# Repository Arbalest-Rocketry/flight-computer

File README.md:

# The Arbalest Goose 4 Avionics Systems & Flight Computer Software by `Leroy Musa`

This repository contains the code and documentation for the flight computer used for our 2 Stage High Power Rocket set to launch at Launch Canada 2024 

## Flight Computer
Our flight computer setup includes two unique PCBs for different rocket stages.

Stage 1 ("BLOB"): This PCB handles all operations for the first stage of the flight, ensuring smooth launch and initial ascent.

Stage 2 (Prototyping Board): This board not only manages the second stage but also controls RunCam devices for onboard video recording. Despite its prototyping nature, it functions just as effectively as the Stage 1 computer.

This dual-PCB setup ensures specialized and reliable performance throughout the entire flight.
<div style="text-align: center;">

</div>

## Components
- Microcontroller: [Teensy 4.1](https://www.pjrc.com/store/teensy41.html)
- Sensors:
  - Altimeter: [Adafruit BMP280](https://www.adafruit.com/product/2651)
  - IMU (Inertial Measurement Unit): [Adafruit BNO055](https://www.adafruit.com/product/4646)
  - GPS Module: [SparkFun GNSS Receiver Breakout - MAX-M10S (Qwiic)](https://www.sparkfun.com/products/18037)
  - SD Breakout: [Adafruit SPI Flash SD Card - XTSD 512 MB](https://www.adafruit.com/product/4899)
- Communication: [Adafruit LoRa RFM9X](https://www.adafruit.com/product/3072)
- Our COTS (Commercial Off-The-Shelf) Flight Computer: [Featherweight Blue Raven](https://www.featherweightaltimeters.com/blue-raven-altimeter.html)
(left)
- Our COTS GPS: [Featherweight GPS Tracker](https://www.featherweightaltimeters.com/featherweight-gps-tracker.html) (right)
<div style="text-align: center;">

</div>

## Avionics Bay Design by `Jordan Birley` and `Caelan Babenko`
The electronics mount CAD design showcases the placement of PCBs within the rocket's fuselage. This design ensures the flight computer's and associated components' proper integration and protection.

<div style="text-align: center;">

</div>

## Testing Setup
Here's an image showing my testing setup for the flight computer(left) and ground station(right):

<div style="text-align: center;">

</div>

## PCBv2.0 Schematics by `Baseer Yousufzai`
Pictures showing our current **Arbalest Flight Computer** schematics layout
<div style="text-align: center;">
  
</div>
<div style="text-align: center;">

</div>

## IRLv2.0
<div style="text-align: center;">

</div>

## PCBv1.0 Schematics by `Baseer Yousufzai`
Pictures showing v1.0 of our **Arbalest Flight Computer** schematics layout
<div style="text-align: center;">
  
</div>
<div style="text-align: center;">

</div>

## IRLv1.0
<div style="text-align: center;">

</div>

## PCB Improvements

This table outlines the major improvements made from PCB v1.0 to PCB v2.0.

| feature                      | pcb v1.0                                  | pcb v2.0                                        | improvement description                                    |
|------------------------------|-------------------------------------------|-------------------------------------------------|------------------------------------------------------------|
| layering                     | single-layer design                       | multi-layer design                              | enhanced routing and reduced interference                  |
| power supply management      | basic power supply connections            | advanced power routing                          | improved power stability and distribution                  |
| lora module         | back right                             | front top right corner                                | better isolation from other components for improved signal quality & better placement for electronics mount                   |

## How it works 
Simple Illustration 
<div style="text-align: center;">
  
</div>

## Arbalest Flight Computer Integration Guide

### Overview

This document provides a detailed description of the Arbalest Flight Computer setup as depicted in the schematic. The system integrates four 3.7V 650mAh LiPo batteries, a screw switch, and three Runcam Split 4 cameras connected to the Arbalest Flight Computer. The flight computer controls four pyro channels specifically designed for parachute deployment.

### Components

1. **Arbalest Flight Computer**
2. **3.7V 650mAh LiPo Batteries (4x)**
3. **Screw Switch**
4. **Runcam Split 4 Cameras (3x)**
5. **Pyro Channels (4x) for Parachute Deployment**

### Wiring Diagram

The wiring diagram consists of the following connections:
- Power supply wiring from the batteries
- Activation of switch wiring
- Camera connections
- Pyro channel connections for parachute deployment

### Power Supply

The power supply section is crucial for powering the flight computer and the connected components.

1. **LiPo Batteries:**
   - Four 3.7V 650mAh LiPo batteries are wired in series parallel to form a 7.4V 1950mAh power pack.
   - **Series Connection:** Two pairs of two batteries connected in series, resulting in two 7.4V packs.
   - **Parallel Connection:** These two 7.4V packs are connected in parallel to increase the capacity to 1950mAh.

2. **Wiring:**
   - The positive terminal of the first battery is connected to the positive terminal of the second battery.
   - The negative terminal of the second battery is connected to the positive terminal of the third battery.
   - The negative terminal of the third battery is connected to the positive terminal of the fourth battery.
   - The negative terminal of the fourth battery is connected back to the system ground.

3. **Screw Switch:**
   - The main power from the batteries is routed through a screw switch to control the power supply to the entire system.
   - The positive wire from the battery pack connects to one terminal of the screw switch.
   - The other terminal of the screw switch connects to the power input of the Arbalest Flight Computer.

### Pyro Channels for Parachute Deployment

The flight computer controls four pyro channels for parachute deployment.

1. **Connections:**
   - Each pyro channel (1 to 4) has two wires: one connected to the flight computer and the other to the pyro device.
   - The flight computer sends a signal to activate the pyrotechnic devices through these wires.

## Conclusion

The integration of the Arbalest Flight Computer with the LiPo batteries, screw switch, Runcam Split 4 cameras, and pyro channels provides a robust system for managing various flight operations, including parachute deployment. 

# Transceiver Test w/ RC plane
<div style="text-align: center;">

</div>

## Low Noise Amplifiers

The low noise amplifiers (LNAs) are crucial components in the Arbalest flight computer's communication system. They are used to amplify weak signals received from the rocket, ensuring they are strong enough to be processed and analyzed. The following images show the setup of the LNAs connected to the Teensy 4.1 microcontroller board:

<div style="text-align: center;">

</div>

### Function of the Low Noise Amplifiers

Low noise amplifiers are designed to amplify weak signals received by the antenna with minimal addition of noise. This is essential in communication systems where signal strength can be significantly reduced due to distance, atmospheric conditions, and other interference factors.

### How the Amplifier and Filter Work

The LNA circuit shown in the images is connected to the LoRa (Long Range) communication module to improve the signal-to-noise ratio. Here’s a detailed explanation of the process:

1. **Signal Reception:**
   - The weak signal received by the antenna is fed into the LNA. This signal is typically very weak and can be easily lost in the noise.

2. **Amplification:**
   - The LNA amplifies the weak signal. The primary goal is to increase the signal strength without adding significant noise. This is achieved through the careful design of the amplifier circuit, using high-quality components that contribute minimal noise.

3. **Filtering:**
   - After amplification, the signal may pass through a filter to remove unwanted frequencies or noise that might have been introduced during amplification. This ensures that only the desired signal is sent to the next stage of the communication system.

4. **Enhanced Signal:**
   - The enhanced signal, now much stronger and clearer, is fed into the LoRa module. The LoRa module can now process this signal more effectively, providing reliable communication over long distances.

### Connecting to LoRa for Increased Gain

The LoRa communication module is known for its ability to transmit data over long distances with low power consumption. By connecting the output of the LNA to the LoRa module, we achieve the following benefits:

- **Increased Range:**
  - The amplified signal can travel greater distances without degradation, improving the overall range of the communication system.

- **Improved Signal Quality:**
  - The higher signal-to-noise ratio achieved through amplification and filtering results in better signal quality, reducing the likelihood of errors in data transmission.

- **Enhanced Reliability:**
  - With stronger and clearer signals, the communication link becomes more reliable, which is critical for mission success in rocketry.

---
# To Infinity and Beyond

---
# Authors
- [Leroy Musa](mailto:musaleroyohio@gmail.com) - Author & Maintainer

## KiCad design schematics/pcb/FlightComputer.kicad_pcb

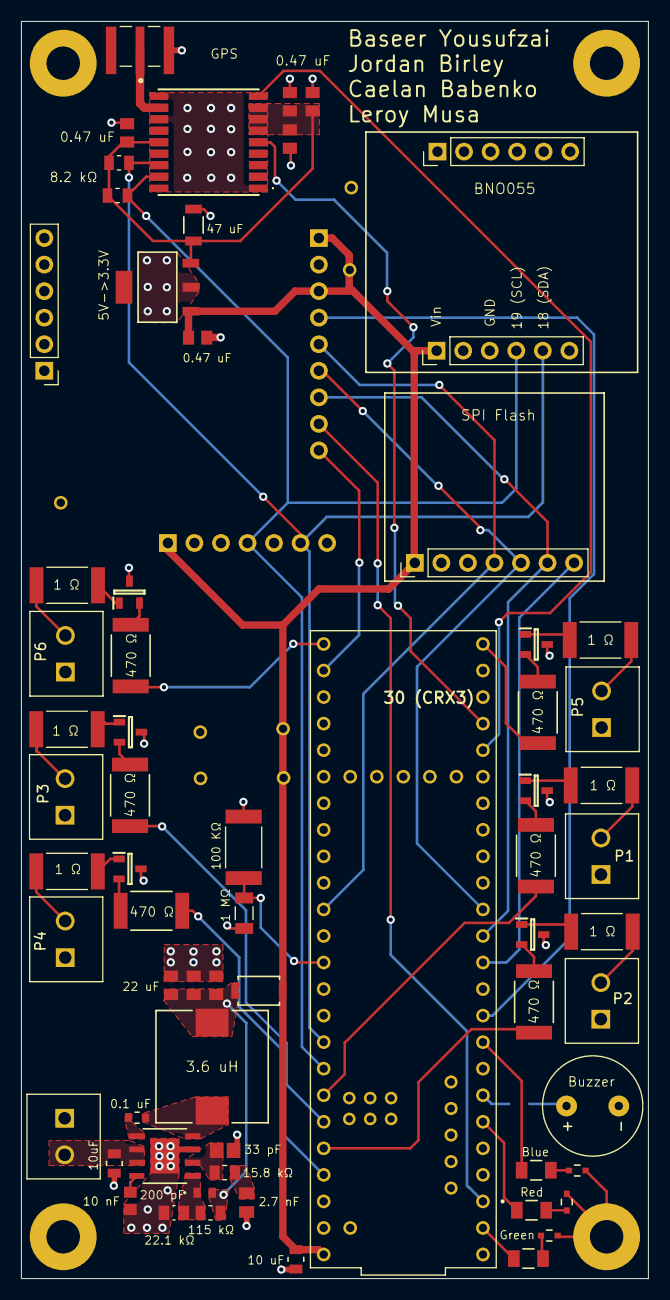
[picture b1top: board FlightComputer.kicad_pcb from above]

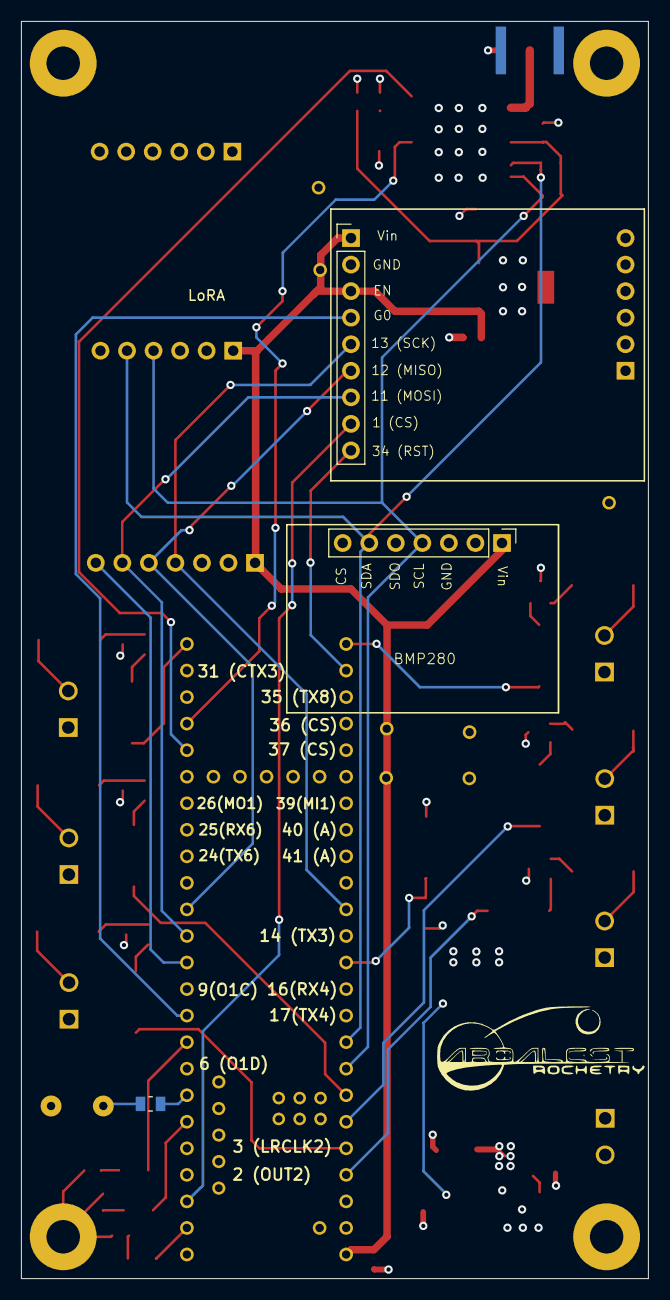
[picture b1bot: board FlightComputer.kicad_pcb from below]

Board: 4 copper layers, 60.0 x 120.3 mm, 73 parts (3 on the bottom side), 57 nets.

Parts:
3.6 uH: 3.6 uH; IND_1064_WE-PDF_WRE
BMP280: PinHeader_1x07_P2.54mm_Vertical
BNO055, BNO085, BNO085#2: PinHeader_1x06_P2.54mm_Vertical
Buzzer: CMI-9605IC-0580T; CUI_CMI-9605IC-0580T
C1: 10uF; CAP_CL21_SAM
C2: 22 uF (Each); CAP_CL_21_SAM
C3, C4: 22 uF; CAP_CL_21_SAM
C5: 10 uF; CAP_CL21_SAM
C7: 47 uF; CAP_CL31_SAM
C8: 33 pF; CAPC220145_88N_KEM
C9: 2.7 nF; CAP_CC0805_YAG
C10, C11, C12, C13, C17: 0.47 uF; CAP_CL_21_SAM
C14: 10 nF; CC0805N_YAG
C15: 0.1 uF; CAP_CL10_SAM
C16: 200 pF; CAP_06033D104JAT2A
H1, H2, H3, H4: MountingHole_Pad; MountingHole_3.2mm_M3_Pad
IC1: MAX-M10S-00B; MAXM10S00B
J1: SMA; TAOGLAS_EMPCB.SMAFSTJ.B.HT
LED1: Red; LED_XZCDG-8VF_SLD
LED2: Green; LED_XZCDG-8VF_SLD
LED4: Blue; LED_XZCDG-8VF_SLD
LoRA: PinHeader_1x09_P2.54mm_Vertical
P1, P2, P3, P4, P5, P6, P7: 1x2 Screw Terminal; OST_OSTTE020104
Q1, Q2, Q3, Q4, Q5, Q6: DMN3051L-7; SOT96P240X110-3N
R1: 1 MΩ; RESC3115X65N
R2: 15.8 kΩ; RESC2012X60N
R3: 22.1 kΩ; RESC2012X65N
R4: 100 KΩ; RESC6332X70N
R5: 324 Ω; RC1206N_VIS
R6, R7: 750 Ω; RC1206N_YAG
R8, R11, R13, R15, R17, R19: 1 Ω; RESC6332X70N
R9, R10, R12, R14, R16, R18: 470 Ω; RES_RMCF2512_STP
R20: 8.2 kΩ; RESC2012X60N
R21: 8.2k Ohm; RESC2012X60N
R22, R22#2: 115 kΩ; RESC2012X60N
R23: Diode; DIO_RB050LAM_ROM
SPI Flash: PinHeader_1x07_P2.54mm_Vertical
U1: Baseer Yousufzai; MODULE_DEV-16771
U2: 5V->3.3V; MP04A
U3: 7.5 V -> 5 V, 5 A; SO-8EP_DIO

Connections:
+3.3V: C7.2, C10.2, C11.2, C12.2, C13.2, IC1.6 (V_BCKP), IC1.7 (V_IO), IC1.8 (VCC), IC1.14 (VCC_RF), R20.2, R21.2, U2.3 (OUT)
+5V: BMP280.1, BNO055.1, C5.2, C17.1, LoRA.1 (VIN), LoRA.3 (EN), R23.1, SPI Flash.1, U1.VIN, U2.1 (IN)
+7.5V: C1.2, P1.1, P2.1, P3.1, P4.1, P5.1, P6.1, P7.2, R1.1, U3.2 (VIN), U3.3 (EN)
/FB: C16.1, R3.2, R22.1, U3.5 (FB)
/Pin 1 (CS): LoRA.8 (CS), U1.1 (TX1)
/Pin 5: Buzzer.P, R22#2.1, R22#2.2, U1.5 (IN2)
/Pin 8 (G0): LoRA.4 (G0), U1.8 (TX2)
/Pin 10 (CS): SPI Flash.7, U1.10 (CS1)
/Pin 11 (MOSI): LoRA.7 (MOSI), SPI Flash.6, U1.11 (MOSI)
/Pin 12 (MISO): LoRA.6 (MISO), SPI Flash.5, U1.12 (MISO)
/Pin 13 (SCK): LoRA.5 (SCK), SPI Flash.4, U1.13 (SCK)
/Pin 15 (A0): R1.2, R4.2, U1.15 (A1)
/Pin 18 (SDA): BMP280.6, BNO055.5, IC1.16 (SDA), R21.1, U1.18 (A4)
/Pin 19 (SCL): BMP280.4, BNO055.4, IC1.17 (SCL), R20.1, U1.19 (A5)
/Pin 20: R9.2, U1.20 (A6)
/Pin 21: R12.2, U1.21 (A7)
/Pin 22: R10.2, U1.22 (A8)
/Pin 23: R14.2, U1.23 (A9)
/Pin 28 (Reset): IC1.9 (RESET_N), U1.28 (RX7)
/Pin 29 (ExtInt): IC1.5 (EXTINT), U1.29 (TX7)
/Pin 32: R16.2, U1.32 (OUT1B)
/Pin 33: R18.2, U1.33 (MCLK2)
/Pin 34 (RST): LoRA.9 (RST), U1.34 (RX8)
/RF: IC1.11 (RF_IN), J1.1
GND: BMP280.3, BMP280.5, BNO055.3, Buzzer.N, C1.1, C2.1, C3.1, C4.1, C5.1, C7.1, C8.1, C9.1, C10.1, C11.1, C12.1, C13.1, C14.1, C17.2, H1.1, H2.1, H3.1, H4.1, IC1.1 (GND_1), IC1.10 (GND_2), IC1.12 (GND_3), J1.SH1, LED1.1, LED2.1, LED4.1, LoRA.2 (GND), P7.1, Q1.3 (D), Q2.3 (D), Q3.3 (D), Q4.3 (D), Q5.3 (D), Q6.3 (D), R3.1, R4.1, SPI Flash.3, U1.GND1 (GND), U1.GND2 (GND), U1.GND3 (GND), U1.GND4 (GND), U1.GND5 (GND), U2.2 (GND), U3.7 (GND), U3.EPAD (GND)
unnamed: C9.2, R2.1
unnamed: 3.6 uH.1, C2.2, C3.2, C4.2, C16.2, R22.2, R23.2
unnamed: LED1.2, R5.2
unnamed: LED2.2, R6.2
unnamed: LED4.2, R7.2
unnamed: P1.2, R8.2
unnamed: P2.2, R11.2
unnamed: P3.2, R13.2
unnamed: P4.2, R15.2
unnamed: P5.2, R17.2
unnamed: P6.2, R19.2
unnamed: Q1.1 (G), R8.1
unnamed: Q1.2 (S), R9.1
unnamed: Q2.1 (G), R11.1
unnamed: Q2.2 (S), R10.1
unnamed: Q3.1 (G), R13.1
unnamed: Q3.2 (S), R12.1
unnamed: Q4.1 (G), R15.1
unnamed: Q4.2 (S), R14.1
unnamed: Q5.1 (G), R17.1
unnamed: Q5.2 (S), R16.1
unnamed: Q6.1 (G), R19.1
unnamed: Q6.2 (S), R18.1
unnamed: U1.3.3V_1 (3.3V), U1.3.3V_2 (3.3V), U1.3.3V_3 (3.3V)
unnamed: R5.1, U1.4 (BCLK2)
unnamed: R6.1, U1.0 (RX1)
unnamed: R7.1, U1.7 (RX2)
unnamed: U1.USB_GND1 (USB_GND), U1.USB_GND2 (USB_GND)
unnamed: C15.1, U3.1 (BST)
unnamed: C8.2, R2.2, U3.6 (COMP)
unnamed: C14.2, U3.4 (SS)
unnamed: 3.6 uH.2, C15.2, U3.8 (SW)

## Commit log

2024-06-02 tree_wide: Added sensor module datasheets
2024-06-03 apogee.cpp; efk.cpp: Implemented Extended Kalman Filter (EKF) using Eigen library for sensor fusion.
2024-06-03 flightcode_main.ino: Refactored code for concise integration of logic through .h files, resolving linker errors caused by redundant object declarations.
2024-06-03 tree_wide: Added credits for PCB Design on README.md
2024-06-03 flightcode_main.ino: Added sequential rocket stage control logic from launch to landing and low power mode.
2024-06-04 tree_wide: Create Structured RunCam Commands Reference TXT File
2024-06-04 flightcode_main.ino: Calculated Expected Response Values for Power On, Power Off, and Start Recording Actions on our RunCam Split 4
2024-06-04 tree_wide: Updated Camera Configuration Naming Convention
2024-06-08 tree_wide: Add images of RunCamSplit4 comparison and connection to flight computer
2024-06-08 tree_wide: Updated README.md to include RunCam config steps.
2024-06-12 refactor: Remove outdated CircuitPython binaries and add MicroPython folder
    - Deleted obsolete adafruit-circuitpython binaries (.hex and .uf2 files) from lib directory
    - Added a new MicroPython folder for RunCam integration
2024-06-12 refactor: Update README.md
2024-06-12 feat: add real-time x-axis visualization script for BNO055 IMU
    This script provides real-time visualization of the x-axis data from the BNO055 IMU.
2024-06-12 feat: Add CircuitPython support for Teensy 4.1 integration
2024-06-12 refactor: adjusted repo structure and added runcams.py
2024-06-18 feat: added working RunCam code
2024-06-18 refactor: added runcam working setup images
2024-06-18 refactor: added current working runcam implementation to flightcode_main.ino
2024-06-18 refactor: directory setup
2024-06-18 refactor: minor changes
2024-06-18 fix: Resolve multiple definition errors in variable declarations
2024-06-18 refactor: Delete __src__/circuitpython directory
2024-06-18 refactor: README update
2024-06-19 feat: modified altimeter kalman filter class - working
2024-06-20 feature: Add sensor initialization and calibration for BNO055
2024-06-20 refactor: added gems
2024-06-20 add: added video of baseer and jordan
2024-06-20 add: added more gems
2024-06-20 fix: Integrate working EKF into flight computer, and enhance logging and transmission
2024-06-23 add: Add GPS feature and integrate initial GPS functionality
2024-06-23 feature: added buzzer song for flight computer start up
2024-06-23 add: Added another song
2024-06-24 add: Add song files to flightcode_main/flightcode_main
2024-06-24 fix: update dependencies for songs
2024-06-26 add: Cleanup and add I2C scanner and IMU test code
2024-06-27 move large files to git-lfs
2024-07-03 Rename __src__ to src
2024-07-03 cleanup
2024-07-04 Add: added featherweight GS V2
2024-07-04 Update README.md to add Featherweight Altimeter GS V2s
2024-07-04 refactor
2024-07-04 Add: Update READme.md to include update PCB schematics
2024-07-04 refactoring: adjusting size and presentation
2024-07-06 add: added updated runcam logic
2024-07-07 lotsa lotsa changes
2024-07-07 polish redundancies
2024-07-07 change acceleration axis based on IMU orientation in rocket
2024-07-08 handled compile errors
2024-07-09 implement rocket states
2024-07-09 correct state machine implementation
2024-07-09 integrate into main code
2024-07-11 cooooooool logo
2024-07-15 add LNA
2024-07-15 add areostructure img
2024-07-15 SD Breakout added
2024-07-19 add working state machine and logging
2024-07-19 redact changes to EKF.ino
2024-07-20 we receive packets till 1km now!!
2024-07-20 added runcam cmd list
2024-07-20 explain pcb v1 --> v2 improvements and changes
2024-07-20 Add July 20th Testing images
2024-07-21 making good progress
2024-07-22 add more documentation
2024-07-23 testing in progress
2024-07-26 Add CircuitPython setup, sensor integration, and SD card logging for Teensy 4.1
    - Install and configure CircuitPython on Teensy 4.1 using HEX firmware
    - Add necessary libraries for BNO055, BMP280, RFM9x, and SD card
    - Integrate BNO055 and BMP280 sensors via I2C
    - Integrate RFM9x LoRa radio module and SD card logging via SPI
    - Document setup instructions and usage in README.md
    - Ensure compatibility with Adafruit SMT SD Card Breakout
2024-07-31 added more gems
2024-08-02 modify low power mode & add mosfet implementation for runcams
2024-08-02 added READMEs for directories
2024-08-04 add AV bay V3
2024-08-04 modify SD files to be more generic
2024-08-06 fixed encapsulation issues and update documentation
2024-08-06 Refactor documentation
2024-08-06 Add finishing touches
2024-08-06 add redundant logic for CAMS to ensure recording
2024-08-15 unified sd logging: timestamp & battery-compatible
2024-08-15 IMU axis remapping
2024-08-16 resolve minor issues
2024-08-20 Axis remap done and transmission modified for compatability w/ Ground Station
